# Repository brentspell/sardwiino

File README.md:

Sardwiino
=========

A wireless interface in a sardine can to a pair of Wii™ nunchuk controllers. For more information, check out [this](http://brentspell.com/blog/sardwiino) post.

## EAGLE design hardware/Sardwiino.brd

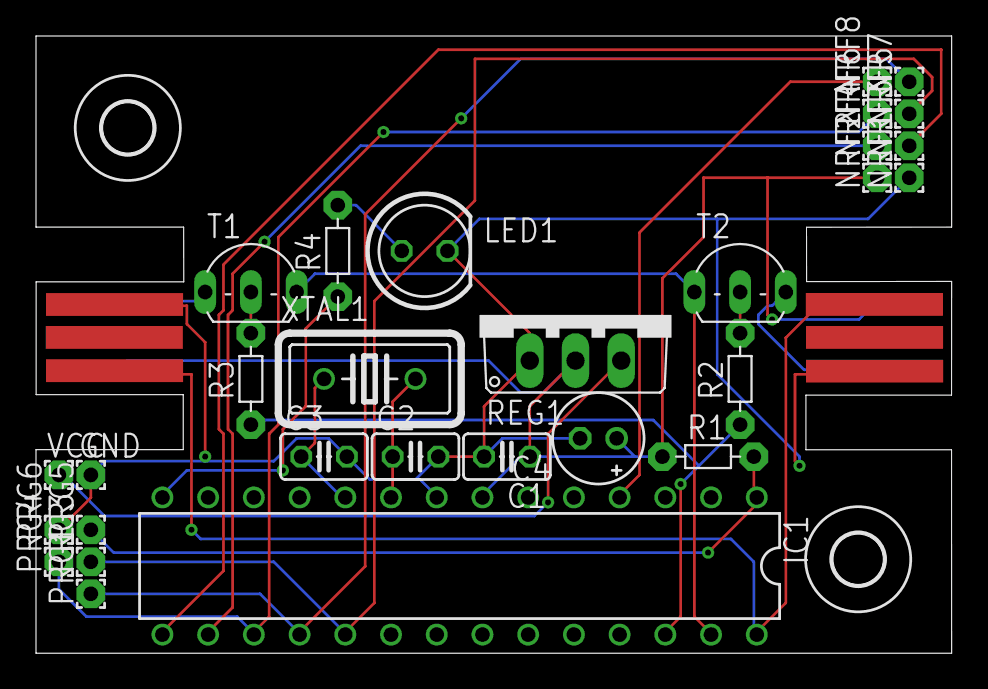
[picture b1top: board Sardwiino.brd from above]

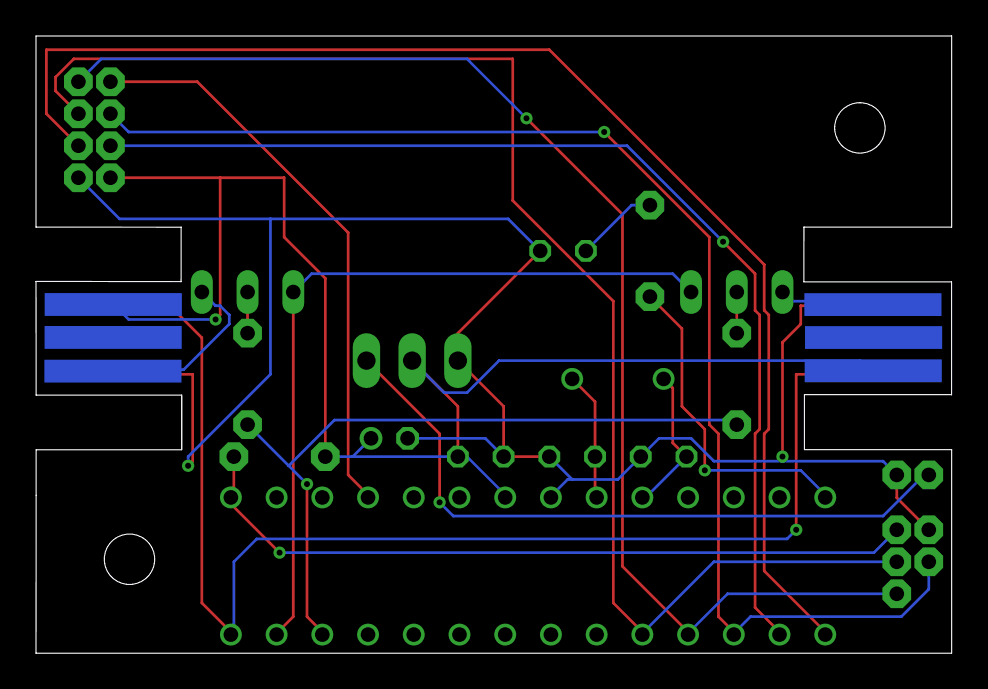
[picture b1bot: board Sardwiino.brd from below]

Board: 2 copper layers, 50.9 x 34.3 mm, 43 parts (6 on the bottom side), 21 nets.

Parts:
C1, C2, C3: C025-025X050
C4: E2-5
E$1, E$3, E$4, E$5, E$6, E$7, E$8, E$9, E$10, E$11, E$12, E$13: WII-NUNCHUK-PAD
E$2, E$14: 2,8
GND: 1,6/0,8
IC1: PDIP-T28
LED1: LED5MM
NR7: 1,6/0,8
NRF1, NRF2, NRF3, NRF4, NRF5, NRF6, NRF8: 1,6/0,8
PRG1, PRG3, PRG4, PRG5, PRG6: 1,6/0,8
R1, R2, R3, R4: R-5
REG1: TO220V
T1, T2: TO92-EBC
VCC: 1,6/0,8
XTAL1: HC18U-V

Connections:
S$2: C1.2, C2.2, C3.2, C4.-, E$6.P$1, E$10.P$1, GND.1, IC1.8, LED1.K, NRF1.1, PRG6.1, REG1.1
S$3: REG1.3, VCC.1
S$4: IC1.26, R2.1, R3.1
S$5: C1.1, C4.+, E$4.P$1, E$13.P$1, IC1.7, NRF2.1, R1.1, REG1.2
S$6: C2.1, IC1.9, XTAL1.2
S$7: C3.1, IC1.10, XTAL1.1
S$8: IC1.1, PRG5.1, R1.2
S$9: R3.2, T1.B
S$10: R2.2, T2.B
S$11: IC1.18, NR7.1, PRG1.1
S$12: IC1.19, NRF5.1, PRG3.1
S$13: IC1.17, NRF6.1, PRG4.1
S$14: IC1.15, NRF3.1
S$15: IC1.16, NRF4.1
S$16: IC1.4, NRF8.1
S$17: E$5.P$1, E$9.P$1, IC1.28
S$18: E$7.P$1, T1.C
S$19: IC1.27, T1.E, T2.C
S$20: E$11.P$1, T2.E
S$21: IC1.14, R4.1
S$22: LED1.A, R4.2

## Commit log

2013-06-26 Initial working version
2013-06-26 Added missing RESET/AVCC connections and eliminated short circuit in off switch
    Resized schematics to conform image sizes
2013-06-26 Changed schematic default colors for clarity
2013-07-01 Added license and link to blog post
2013-11-27 Merged changes from home project
2014-02-04 Added board for the Sardwiino
